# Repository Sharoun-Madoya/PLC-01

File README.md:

# PLC-01
BC848CDW1T1- transistor , power surface mount for amplification 
 DS1307ZN_ real time clock, 56 byte ram for data storage
 SLPRT5V0U2X low capacitance electrostatic discharge  protection diode  meant to protect two high frequency signls  from damage \

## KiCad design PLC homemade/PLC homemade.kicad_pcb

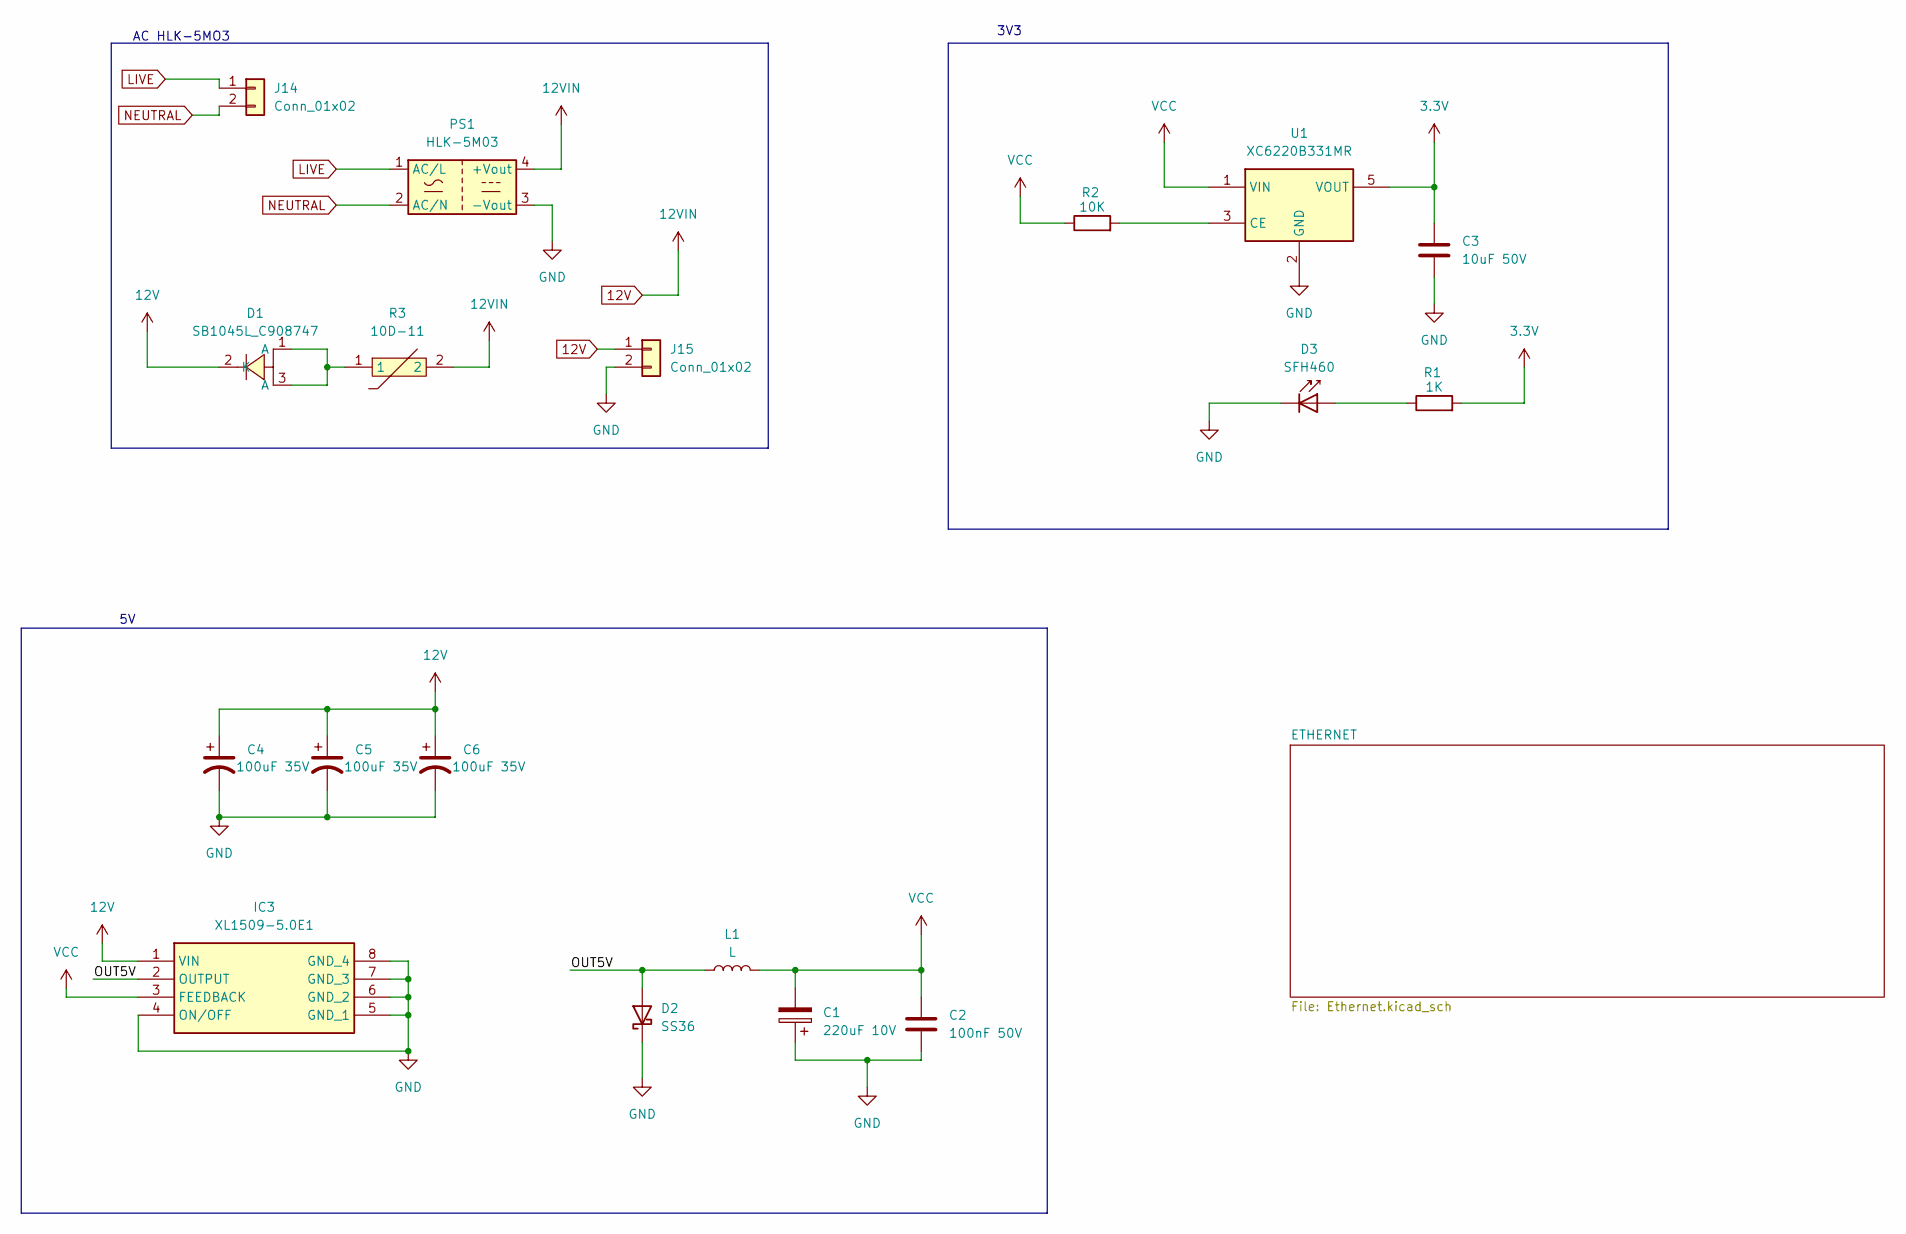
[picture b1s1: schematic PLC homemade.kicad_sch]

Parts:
C1: 220uF 10V; C_0201_0603Metric
C2: 100nF 50V; C_0201_0603Metric
C3: 10uF 50V; C_01005_0402Metric
C4, C5, C6: 100uF 35V; C_0201_0603Metric
D1: SB1045L_C908747; TO-277_3P-L5.4-W4.0-LS6.5-TR; LCSC Part C908747
D2: SS36; D_SMA
D3: SFH460; TO-18-2_Window
IC3: XL1509-5.0E1; SOIC127P600X175-8N; Manufacturer_Part_Number XL1509-5.0E1
J14: Conn_01x02; PhoenixContact_MCV_1,5_2-GF-3.81_1x02_P3.81mm_Vertical_Thre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
J15: Conn_01x02; PhoenixContact_GMSTBA_2,5_2-G_1x02_P7.50mm_Horizontal
L1: L; L_APV_APH1040
PS1: HLK-5M03; Converter_ACDC_Hi-Link_HLK-5Mxx
R1: 1K; Crystal_SMD_5032-2Pin_5.0x3.2mm
R2: 10K; R_01005_0402Metric
R3: 10D-11; RES-TH_L12.5-W5.5-P7.50-D0.8-S5.50; LCSC Part C53820
U1: XC6220B331MR; SOT-23-5

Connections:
3.3V: C3.1, R1.2, U1.5 (VOUT); also elsewhere on the board
12V: C4.1, C5.1, C6.1, D1.2 (K), IC3.1 (VIN), J15.1, PS1.4 (+Vout), R3.2; also elsewhere on the board
/OUT5V: D2.2 (A), IC3.2 (OUTPUT), L1.1
AGND: C1.1, C2.2, C3.2, C4.2, C5.2, C6.2, D2.1 (K), D3.1 (K), IC3.4 (ON/OFF), IC3.5 (GND_1), IC3.6 (GND_2), IC3.7 (GND_3), IC3.8 (GND_4), J15.2, PS1.3 (-Vout), U1.2 (GND); also elsewhere on the board
LIVE: J14.1, PS1.1 (AC/L)
NEUTRAL: J14.2, PS1.2 (AC/N)
unnamed: D1.1 (A), D1.3 (A), R3.1
unnamed: D3.2 (A), R1.1
unnamed: R2.2, U1.3 (CE)
VCC: C1.2, C2.1, IC3.3 (FEEDBACK), L1.2, R2.1, U1.1 (VIN); also elsewhere on the board

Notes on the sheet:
3V3
AC HLK-5MO3

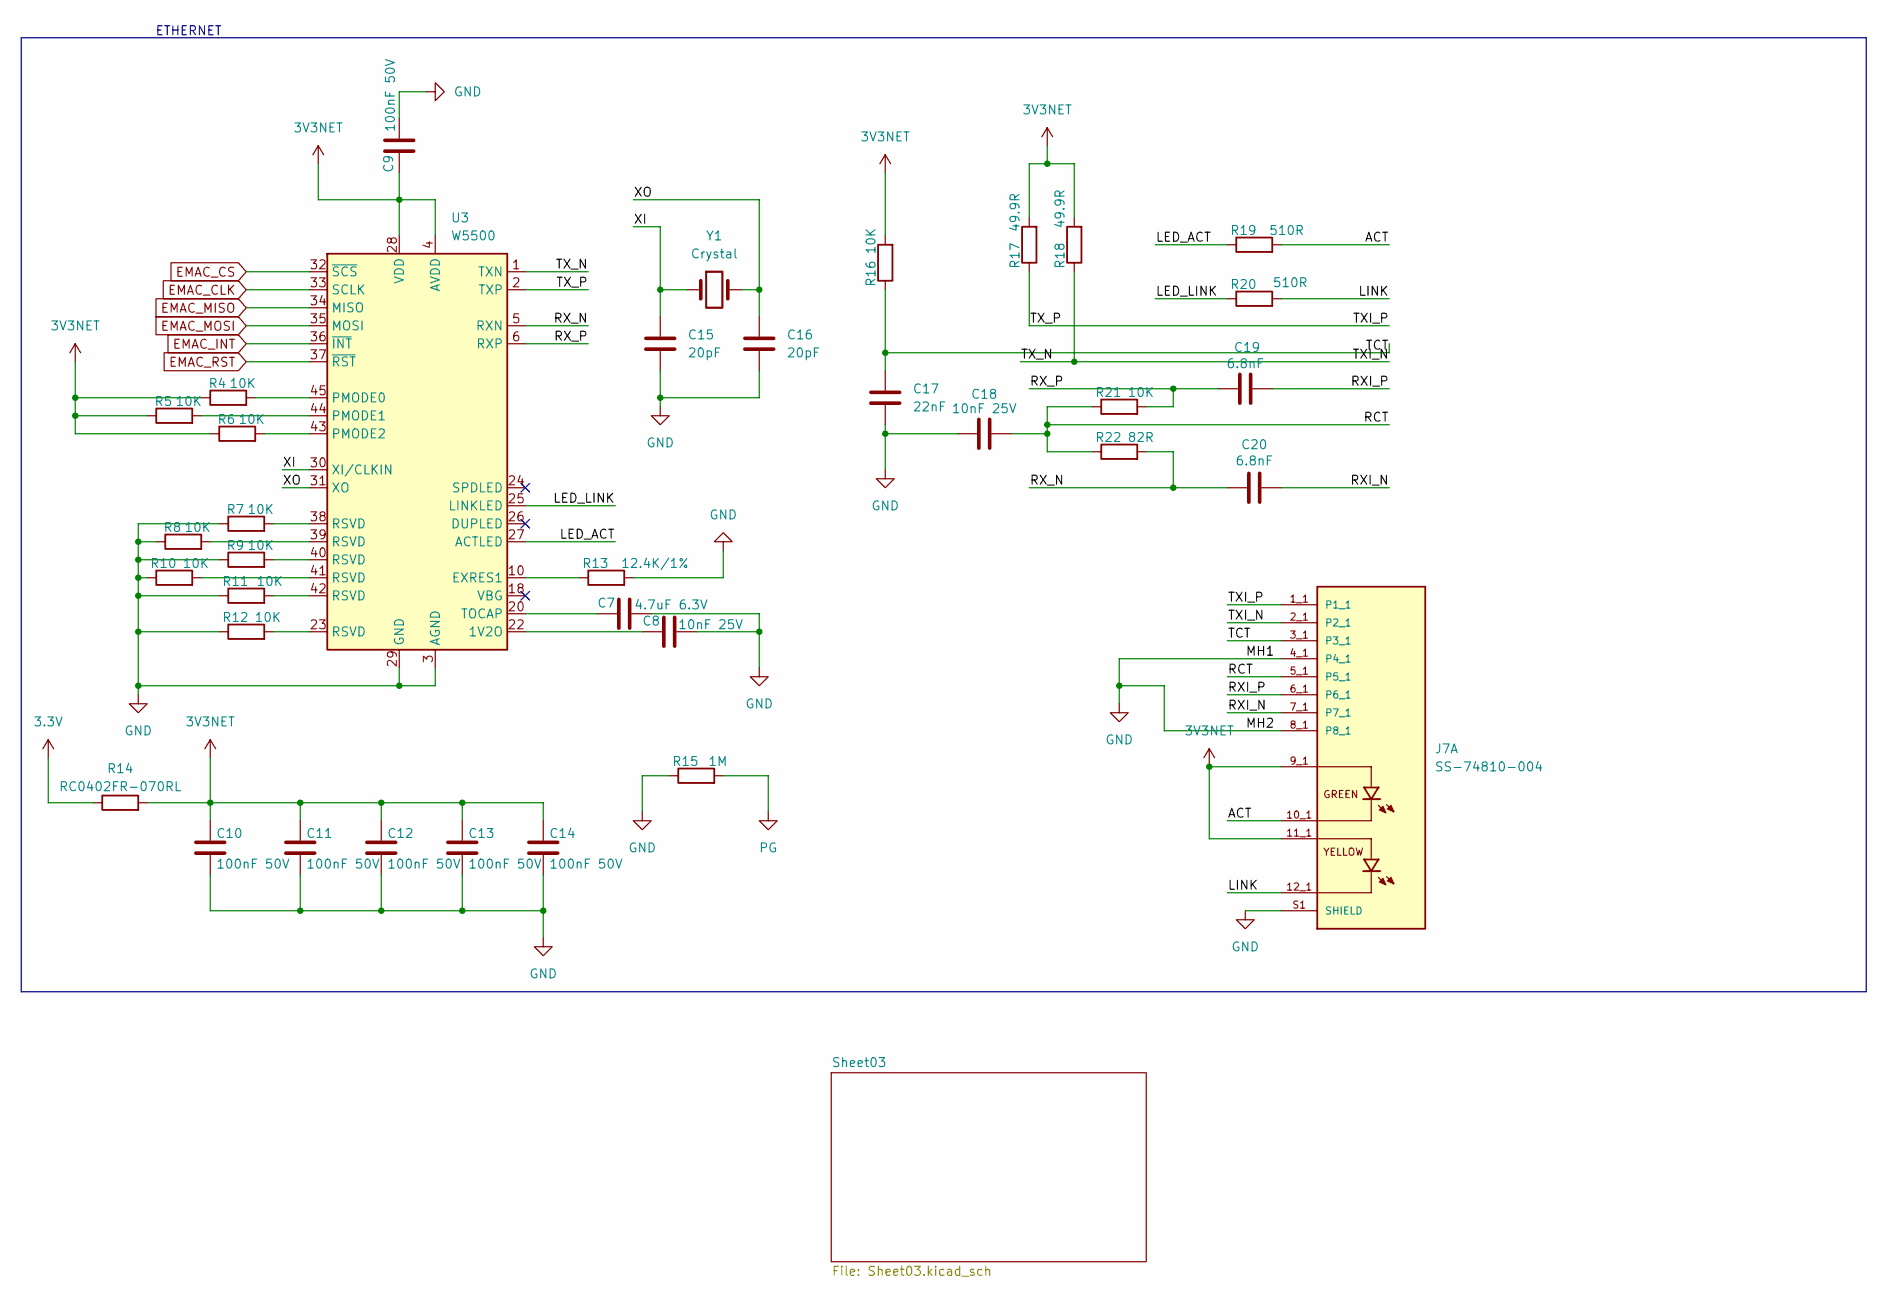
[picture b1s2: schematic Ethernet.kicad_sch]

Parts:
C7: 4.7uF 6.3V; C_01005_0402Metric
C8, C18: 10nF 25V; C_01005_0402Metric
C9, C10, C11, C12, C13, C14: 100nF 50V; C_01005_0402Metric
C15, C16: 20pF; C_01005_0402Metric
C17: 22nF; C_01005_0402Metric
C19, C20: 6.8nF; C_01005_0402Metric
J7: SS-74810-004; BEL_SS-74810-004; PARTREV A0
R4, R5, R6, R7, R8, R9, R10, R11, R12, R16, R21: 10K; R_01005_0402Metric
R13: 12.4K/1%; R_01005_0402Metric
R14: RC0402FR-070RL; R_01005_0402Metric
R15: 1M; R_01005_0402Metric
R17, R18: 49.9R; R_1206_3216Metric
R19, R20: 510R; R_1206_3216Metric
R22: 82R; R_1206_3216Metric
U3: W5500; LQFP-48_7x7mm_P0.5mm
Y1: Crystal; Crystal_SMD_5032-2Pin_5.0x3.2mm

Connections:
3.3V: R14.1; also elsewhere on the board
3V3NET: C9.1, C10.1, C11.1, C12.1, C13.1, C14.1, J7.9_1, J7.11_1, R4.1, R5.1, R6.1, R14.2, R16.2, R17.2, R18.2, U3.4 (AVDD), U3.8 (AVDD), U3.11 (AVDD), U3.15 (AVDD), U3.17 (AVDD), U3.21 (AVDD), U3.28 (VDD)
/ETHERNET/ACT: J7.10_1, R19.2
/ETHERNET/LED_ACT: R19.1, U3.27 (ACTLED)
/ETHERNET/LED_LINK: R20.1, U3.25 (LINKLED)
/ETHERNET/LINK: J7.12_1, R20.2
/ETHERNET/RCT: C18.2, J7.5_1, R21.1, R22.1
/ETHERNET/RXI_N: C20.2, J7.7_1
/ETHERNET/RXI_P: C19.2, J7.6_1
/ETHERNET/RX_N: C20.1, R22.2, U3.5 (RXN)
/ETHERNET/RX_P: C19.1, R21.2, U3.6 (RXP)
/ETHERNET/TCT: C17.1, J7.3_1, R16.1
/ETHERNET/TXI_N: J7.2_1, R18.1, U3.1 (TXN)
/ETHERNET/TXI_P: J7.1_1, R17.1, U3.2 (TXP)
/ETHERNET/XI: C15.1, U3.30 (XI/CLKIN), Y1.1
/ETHERNET/XO: C16.1, U3.31 (XO), Y1.2
AGND: C7.2, C8.2, C9.2, C10.2, C11.2, C12.2, C13.2, C14.2, C15.2, C16.2, C17.2, C18.1, J7.4_1, J7.8_1, J7.S1 (SHIELD), J7.S2 (SHIELD), J7.S3 (SHIELD), J7.S4 (SHIELD), J7.S5 (SHIELD), J7.S6 (SHIELD), J7.S7 (SHIELD), J7.S8 (SHIELD), J7.S9 (SHIELD), R7.1, R8.1, R9.1, R10.1, R11.1, R12.1, R13.2, R15.1, U3.3 (AGND), U3.9 (AGND), U3.14 (AGND), U3.16 (AGND), U3.19 (AGND), U3.29 (GND), U3.48 (AGND); also elsewhere on the board
EMAC_CLK: U3.33 (SCLK); also elsewhere on the board
EMAC_CS: U3.32 (~SCS); also elsewhere on the board
EMAC_INT: U3.36 (~INT); also elsewhere on the board
EMAC_MISO: U3.34 (MISO); also elsewhere on the board
EMAC_MOSI: U3.35 (MOSI); also elsewhere on the board
EMAC_RST: U3.37 (~RST); also elsewhere on the board
unnamed: R7.2, U3.38 (RSVD)
unnamed: R8.2, U3.39 (RSVD)
unnamed: R9.2, U3.40 (RSVD)
unnamed: R10.2, U3.41 (RSVD)
unnamed: R11.2, U3.42 (RSVD)
unnamed: R12.2, U3.23 (RSVD)
unnamed: C8.1, U3.22 (1V2O)
unnamed: R13.1, U3.10 (EXRES1)
unnamed: R4.2, U3.45 (PMODE0)
unnamed: R5.2, U3.44 (PMODE1)
unnamed: R6.2, U3.43 (PMODE2)
unnamed: C7.1, U3.20 (TOCAP)
PG: R15.2

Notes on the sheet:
ETHERNET

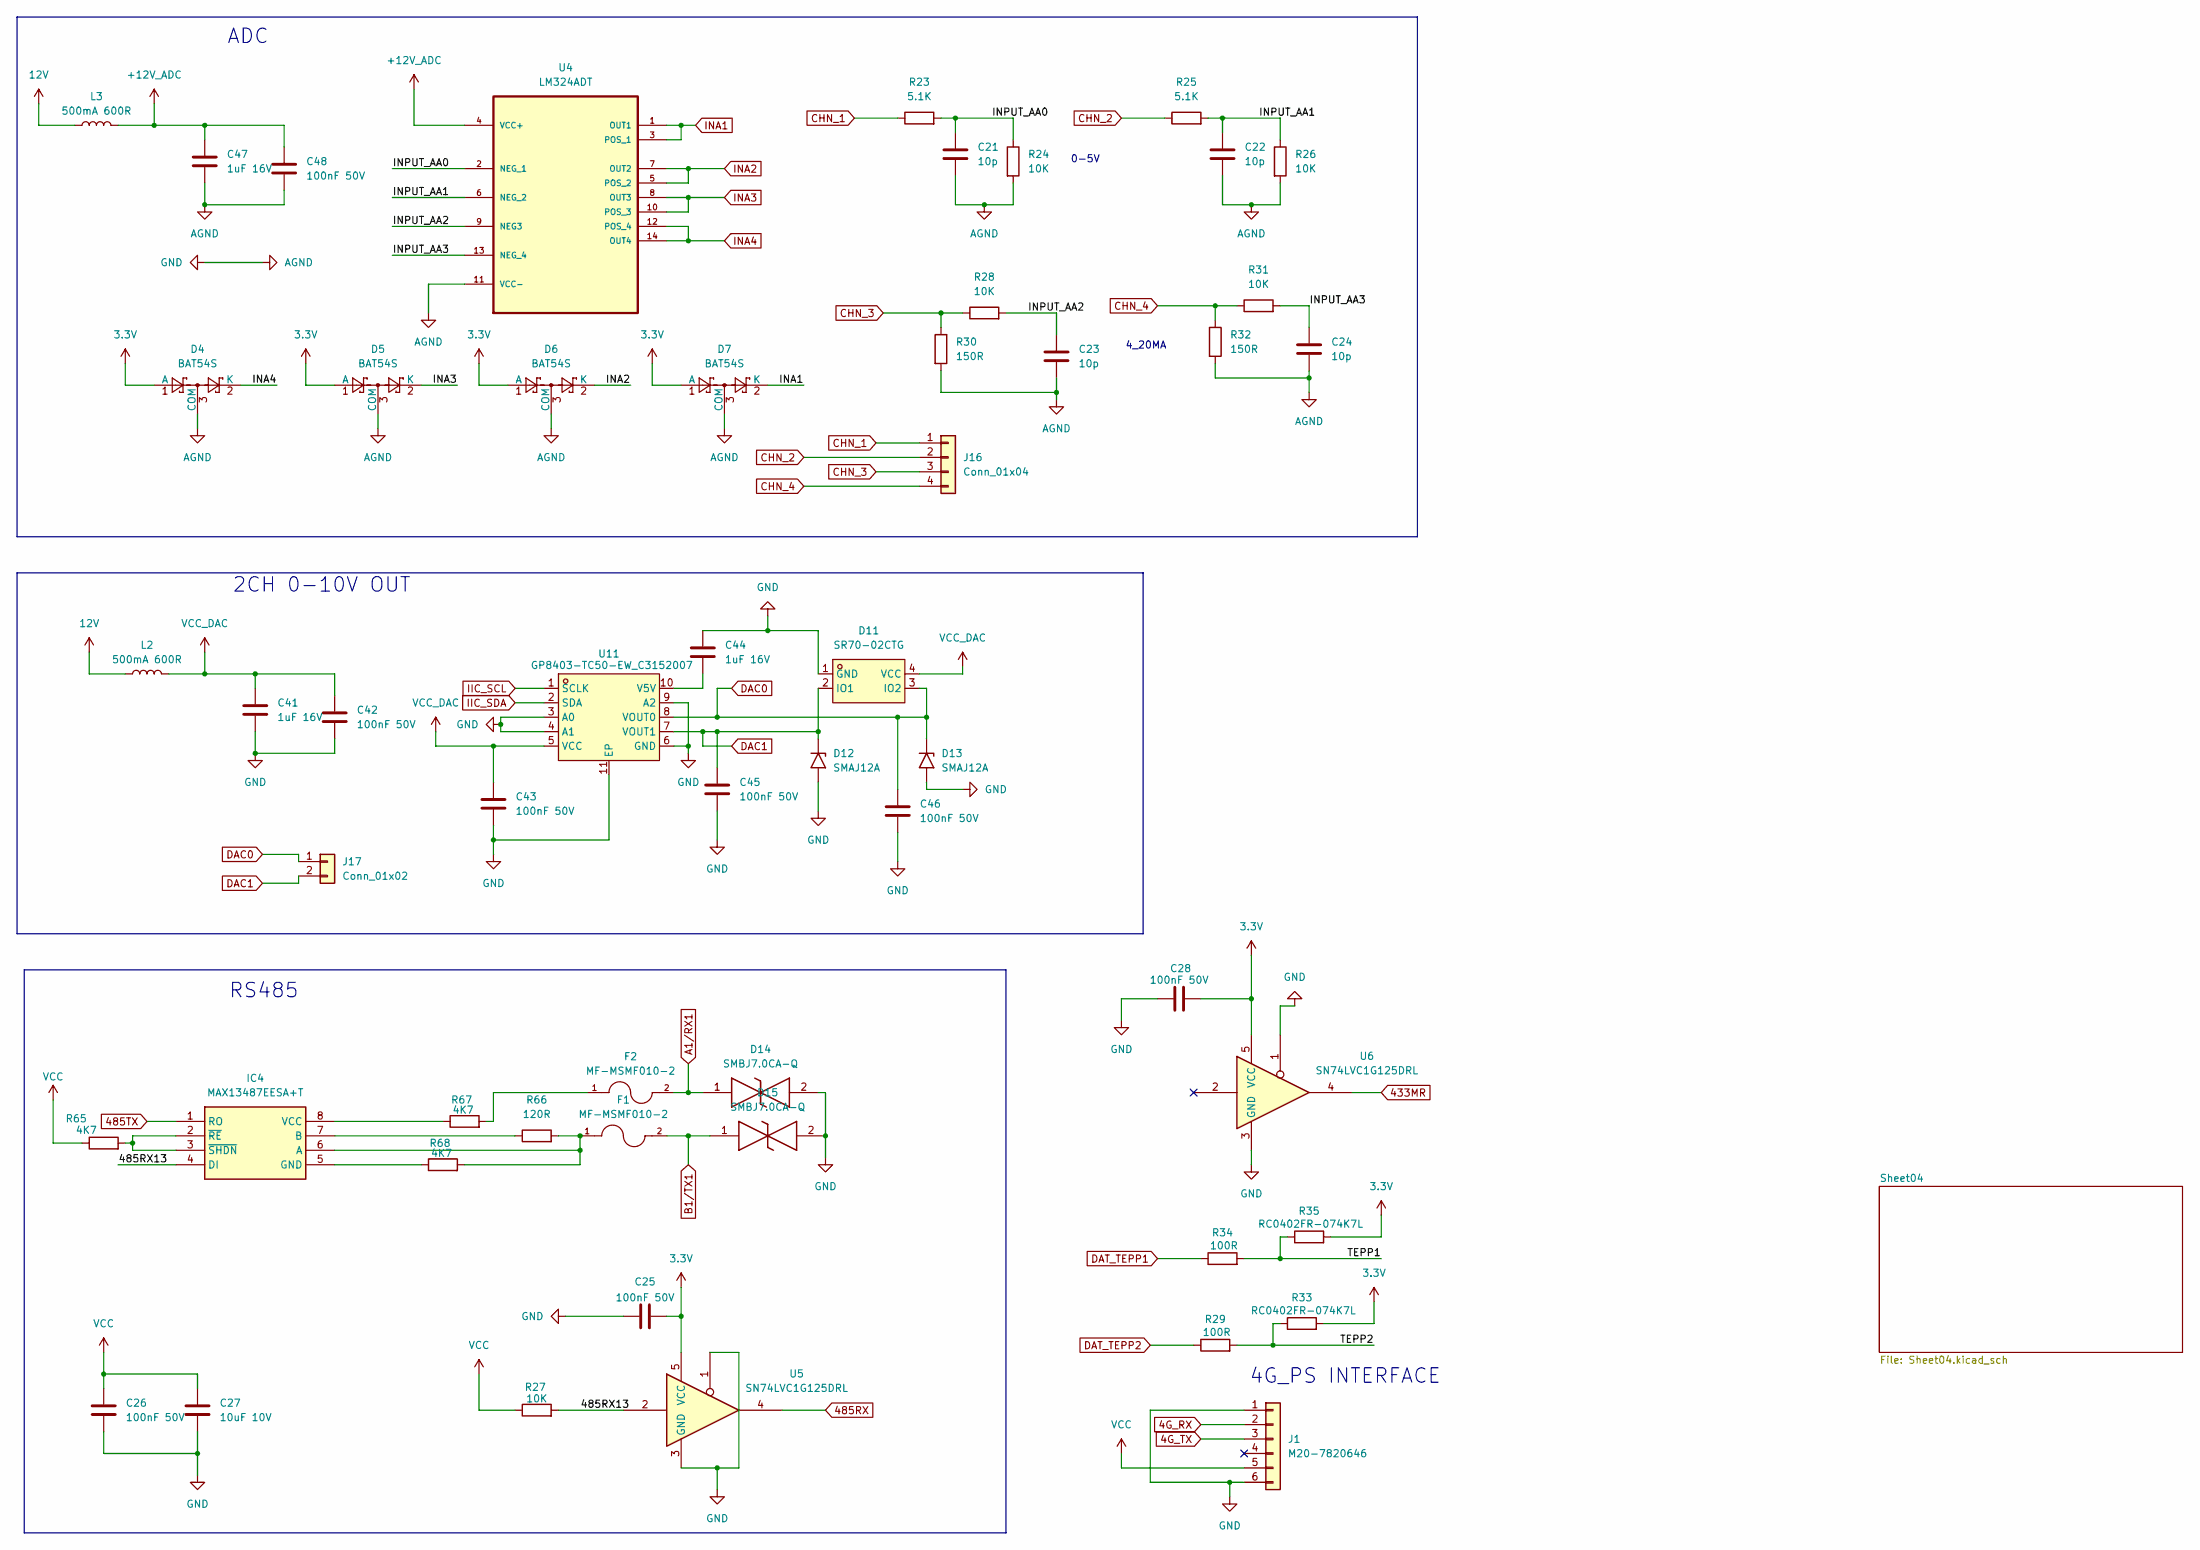
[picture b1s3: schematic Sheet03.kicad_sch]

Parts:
C21, C22, C23, C24: 10p; C_01005_0402Metric
C25, C26, C28, C42, C43, C45, C46: 100nF 50V; C_01005_0402Metric
C27: 10uF 10V; C_0201_0603Metric
C41, C44, C47: 1uF 16V; C_0201_0603Metric
C48: 100nF 50V; C_0201_0603Metric
D4, D5, D6, D7: BAT54S; SOT-23
D11: SR70-02CTG; SOT-143-4_L2.9-W1.3-P1.92-LS2.4-BL; LCSC Part C1973334
D12, D13: SMAJ12A; D_SMA
D14, D15: SMBJ7.0CA-Q; DIONM5436X244N; Manufacturer_Part_Number SMBJ7.0CA-Q
F1, F2: MF-MSMF010-2; FUSER_MF-MSMF010-2
IC4: MAX13487EESA+T; SOIC127P600X175-8N; Manufacturer_Part_Number MAX13487EESA+T; Mouser Part Number 700-MAX13487EESAT
J1: M20-7820646; HARWIN_M20-7820646
J16: Conn_01x04; PinHeader_1x04_P2.00mm_Vertical
J17: Conn_01x02; PinHeader_1x02_P2.00mm_Vertical
L2, L3: 500mA 600R; L_APV_APH1040
R23, R25: 5.1K; R_1206_3216Metric
R24, R26, R27, R28, R31: 10K; R_01005_0402Metric
R29, R34: 100R; R_1206_3216Metric
R30, R32: 150R; R_1206_3216Metric
R33, R35: RC0402FR-074K7L; R_1206_3216Metric
R65, R67, R68: 4K7; R_01005_0402Metric
R66: 120R; R_1206_3216Metric
U4: LM324ADT; SOIC127P600X175-14N; MPN LM324ADT
U5, U6: SN74LVC1G125DRL; Texas_R-PDSO-N5_DRL-5
U11: GP8403-TC50-EW_C3152007; ESSOP-10_L4.9-W3.9-P1.00-LS6.0-BL-EP; LCSC Part C3152007

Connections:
3.3V: C25.2, C28.2, D4.1 (A), D5.1 (A), D6.1 (A), D7.1 (A), R33.2, R35.2, U5.5 (VCC), U6.5 (VCC); also elsewhere on the board
4G_RX: J1.2
4G_TX: J1.3
12V: L2.1, L3.1; also elsewhere on the board
433MR: U6.4
485RX: U5.4; also elsewhere on the board
485TX: IC4.1 (RO); also elsewhere on the board
+12V_ADC: C47.1, C48.1, L3.2, U4.4 (VCC+)
/ETHERNET/Sheet03/485RX13: IC4.4 (DI), R27.2, U5.2
/ETHERNET/Sheet03/INPUT_AA0: C21.1, R23.2, R24.1, U4.2 (NEG_1)
/ETHERNET/Sheet03/INPUT_AA1: C22.1, R25.2, R26.1, U4.6 (NEG_2)
/ETHERNET/Sheet03/INPUT_AA2: C23.1, R28.2, U4.9 (NEG3)
/ETHERNET/Sheet03/INPUT_AA3: C24.1, R31.2, U4.13 (NEG_4)
/ETHERNET/Sheet03/TEPP1: R34.2, R35.1
/ETHERNET/Sheet03/TEPP2: R29.2, R33.1
A1/RX1: D14.1, F2.2
AGND: C21.2, C22.2, C23.2, C24.2, C25.1, C26.2, C27.2, C28.1, C41.2, C42.2, C43.2, C44.2, C45.2, C46.2, C47.2, C48.2, D4.3 (COM), D5.3 (COM), D6.3 (COM), D7.3 (COM), D11.1 (GND), D12.2 (A2), D13.2 (A2), D14.2, D15.2, J1.1, J1.6, R24.2, R26.2, R30.2, R32.2, U4.11 (VCC-), U5.1, U5.3 (GND), U6.1, U6.3 (GND), U11.3 (A0), U11.4 (A1), U11.6 (GND), U11.9 (A2), U11.11 (EP); also elsewhere on the board
B1/TX1: D15.1, F1.2
CHN_1: J16.1, R23.1
CHN_2: J16.2, R25.1
CHN_3: J16.3, R28.1, R30.1
CHN_4: J16.4, R31.1, R32.1
DAC0: C46.1, D11.3 (IO2), D13.1 (A1), J17.1, U11.8 (VOUT0)
DAC1: C45.1, D11.2 (IO1), D12.1 (A1), J17.2, U11.7 (VOUT1)
DAT_TEPP1: R34.1; also elsewhere on the board
DAT_TEPP2: R29.1; also elsewhere on the board
IIC_SCL: U11.1 (SCLK); also elsewhere on the board
IIC_SDA: U11.2 (SDA); also elsewhere on the board
INA1: D7.2 (K), U4.1 (OUT1), U4.3 (POS_1); also elsewhere on the board
INA2: D6.2 (K), U4.5 (POS_2), U4.7 (OUT2); also elsewhere on the board
INA3: D5.2 (K), U4.8 (OUT3), U4.10 (POS_3); also elsewhere on the board
INA4: D4.2 (K), U4.12 (POS_4), U4.14 (OUT4); also elsewhere on the board
unnamed: F2.1, R67.2
unnamed: F1.1, IC4.6 (A), R66.2, R68.2
unnamed: IC4.7 (B), R66.1
unnamed: IC4.5 (GND), R68.1
unnamed: IC4.8 (VCC), R67.1
unnamed: IC4.2 (~RE), IC4.3 (~SHDN), R65.2
unnamed: C44.1, U11.10 (V5V)
VCC: C26.1, C27.1, J1.5, R27.1, R65.1; also elsewhere on the board
VCC_DAC: C41.1, C42.1, C43.1, D11.4 (VCC), L2.2, U11.5 (VCC)

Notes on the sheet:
RS485
0-5V
2CH 0-10V OUT
4_20MA
4G_PS INTERFACE
ADC

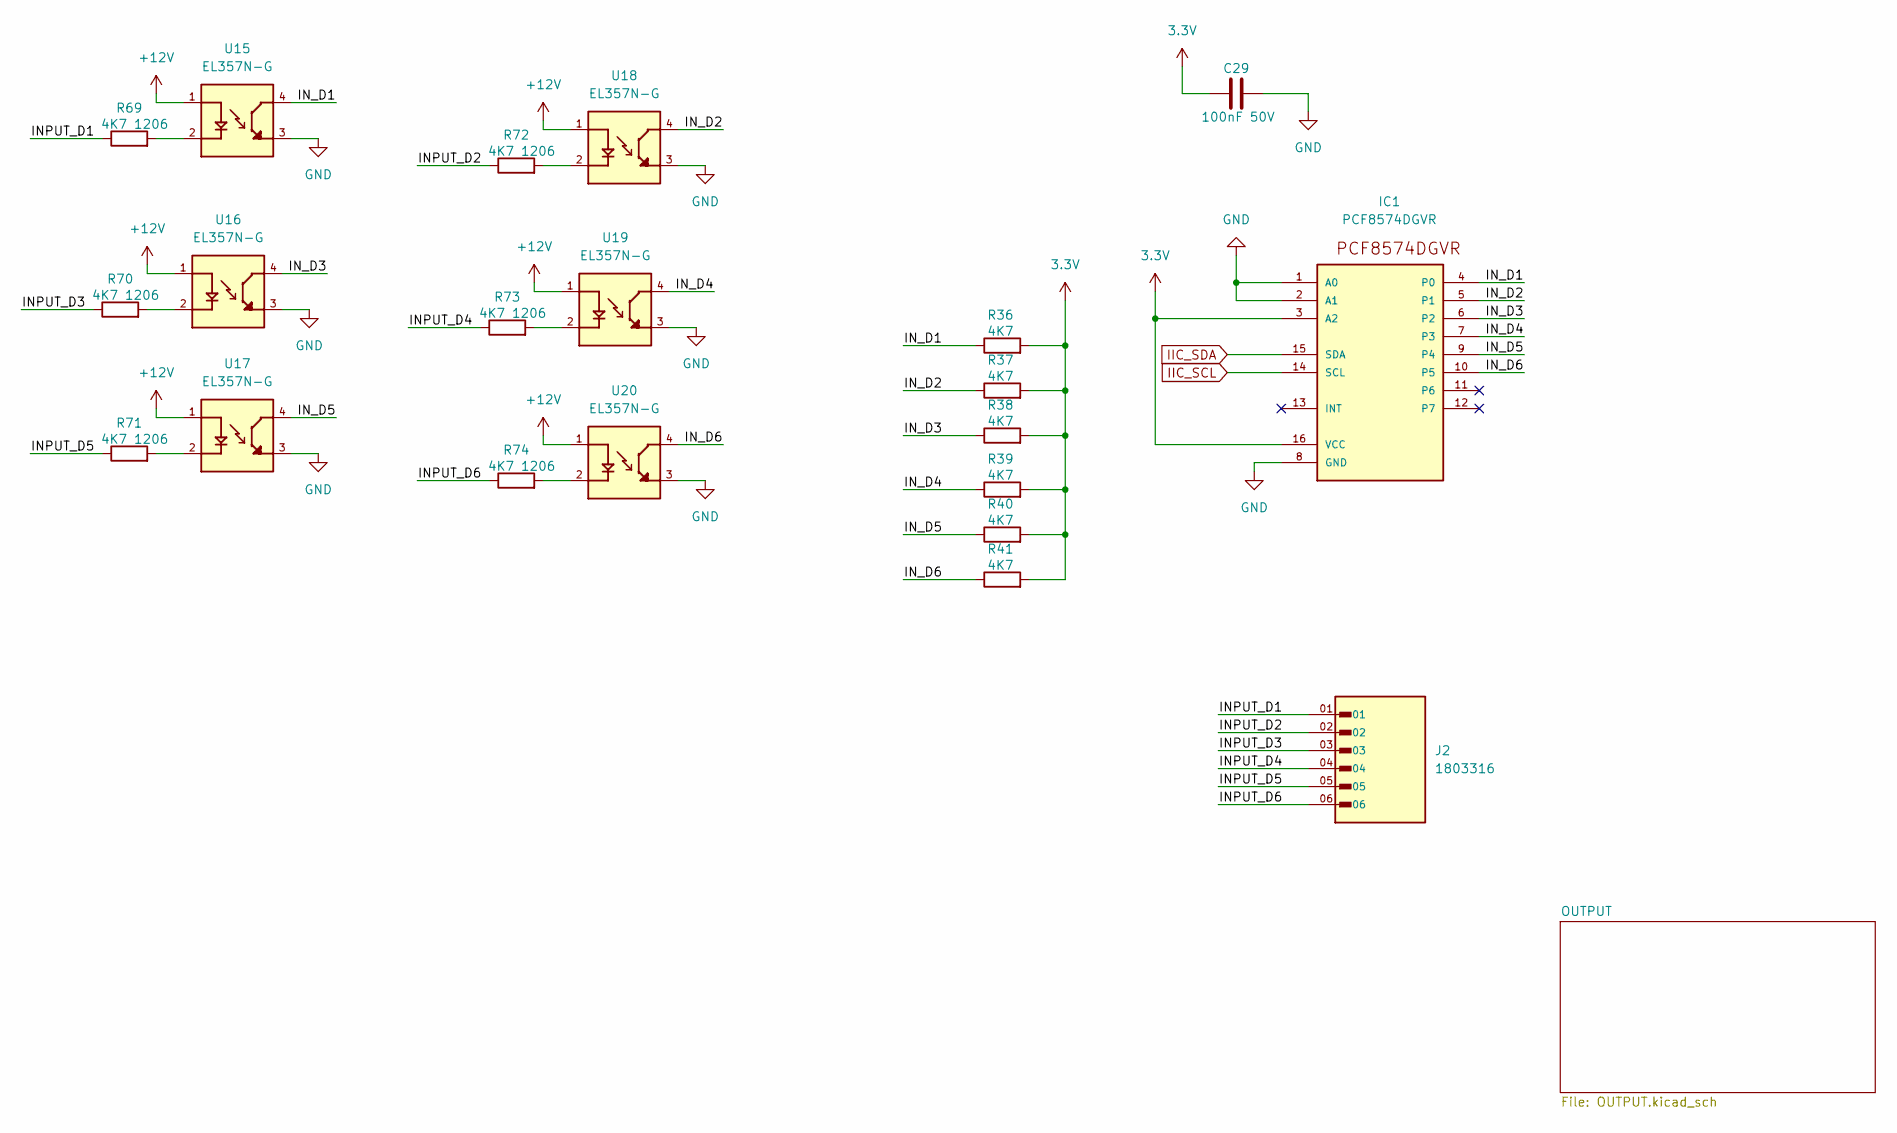
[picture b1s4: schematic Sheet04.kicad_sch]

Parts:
C29: 100nF 50V; C_01005_0402Metric
IC1: PCF8574DGVR; DIL16
J2: 1803316; PHOENIX_1803316; PARTREV 08.06.2015
R36, R37, R38, R39, R40, R41: 4K7; R_01005_0402Metric
R69, R70, R71, R72, R73, R74: 4K7 1206; R_01005_0402Metric
U15, U16, U17, U18, U19, U20: EL357N-G; OPTO_EL357N-G; PARTREV 6

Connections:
3.3V: C29.1, IC1.3 (A2), IC1.16 (VCC), R36.2, R37.2, R38.2, R39.2, R40.2, R41.2; also elsewhere on the board
+12V: U15.1, U16.1, U17.1, U18.1, U19.1, U20.1
/ETHERNET/Sheet03/Sheet04/INPUT_D1: J2.01, R69.1
/ETHERNET/Sheet03/Sheet04/INPUT_D2: J2.02, R72.1
/ETHERNET/Sheet03/Sheet04/INPUT_D3: J2.03, R70.1
/ETHERNET/Sheet03/Sheet04/INPUT_D4: J2.04, R73.1
/ETHERNET/Sheet03/Sheet04/INPUT_D5: J2.05, R71.1
/ETHERNET/Sheet03/Sheet04/INPUT_D6: J2.06, R74.1
/ETHERNET/Sheet03/Sheet04/IN_D1: IC1.4 (P0), R36.1, U15.4
/ETHERNET/Sheet03/Sheet04/IN_D2: IC1.5 (P1), R37.1, U18.4
/ETHERNET/Sheet03/Sheet04/IN_D3: IC1.6 (P2), R38.1, U16.4
/ETHERNET/Sheet03/Sheet04/IN_D4: IC1.7 (P3), R39.1, U19.4
/ETHERNET/Sheet03/Sheet04/IN_D5: IC1.9 (P4), R40.1, U17.4
/ETHERNET/Sheet03/Sheet04/IN_D6: IC1.10 (P5), R41.1, U20.4
AGND: C29.2, IC1.1 (A0), IC1.2 (A1), IC1.8 (GND), U15.3, U16.3, U17.3, U18.3, U19.3, U20.3; also elsewhere on the board
IIC_SCL: IC1.14 (SCL); also elsewhere on the board
IIC_SDA: IC1.15 (SDA); also elsewhere on the board
unnamed: R69.2, U15.2
unnamed: R70.2, U16.2
unnamed: R71.2, U17.2
unnamed: R72.2, U18.2
unnamed: R73.2, U19.2
unnamed: R74.2, U20.2

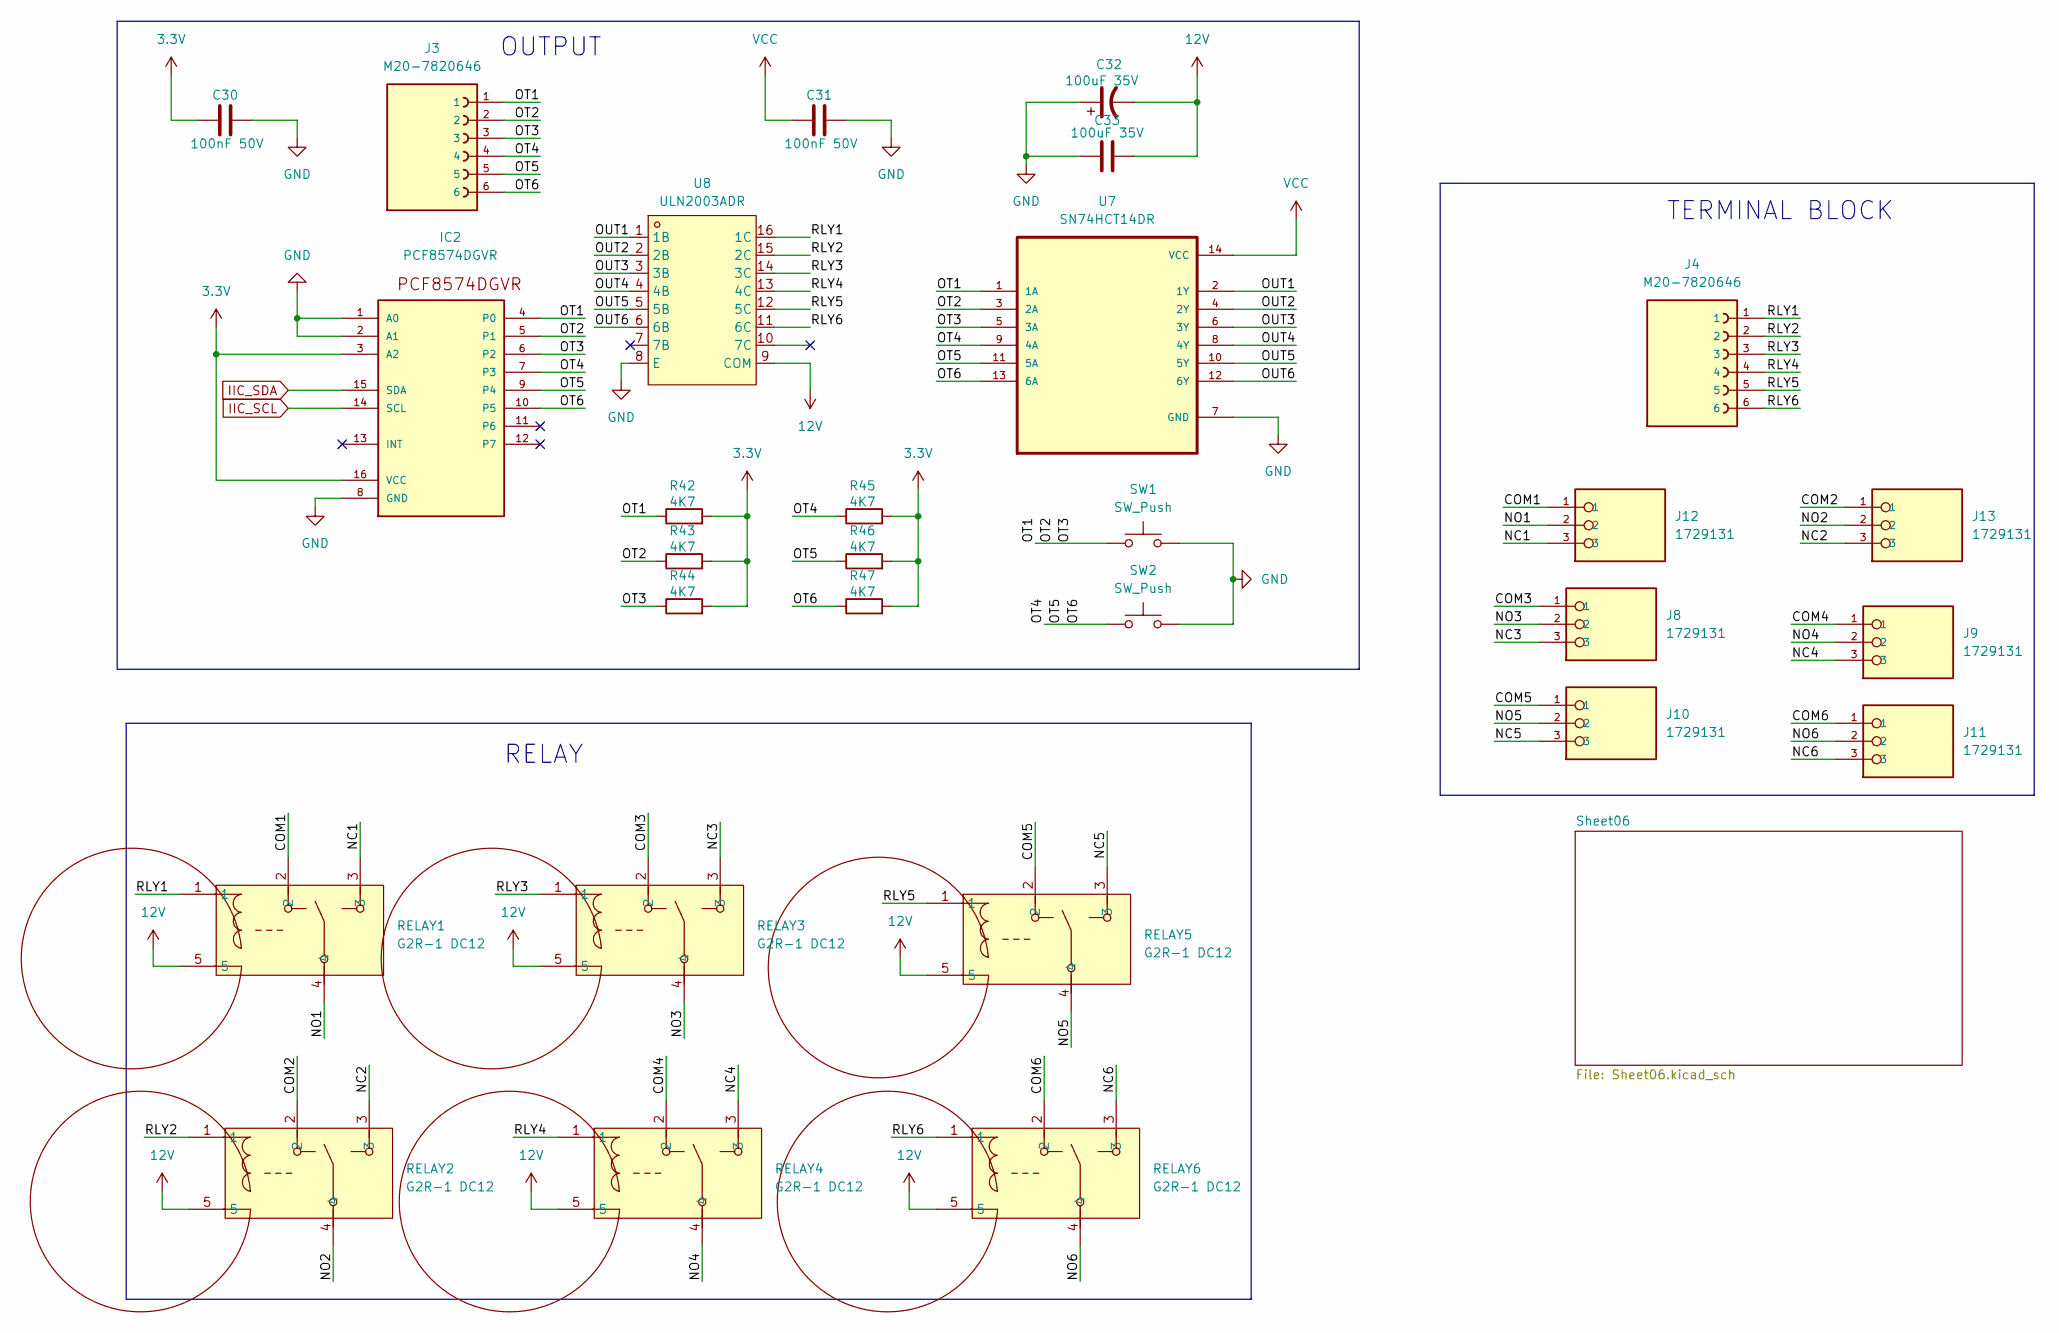
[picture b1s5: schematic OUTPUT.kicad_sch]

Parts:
C30, C31: 100nF 50V; C_01005_0402Metric
C32: 100uF 35V; CP_Elec_10x7.7
C33: 100uF 35V; C_0201_0603Metric
IC2: PCF8574DGVR; DIL16
J3, J4: M20-7820646; HARWIN_M20-7820646
J8, J9, J10, J11, J12, J13: 1729131; PHOENIX_1729131
R42, R43, R44, R45, R46, R47: 4K7; R_01005_0402Metric
RELAY1, RELAY2, RELAY3, RELAY4, RELAY5, RELAY6: G2R-1 DC12; RELAY-TH_G2R-1; LCSC Part C2750337
SW1, SW2: SW_Push; SW_SPST_TL3305A
U7: SN74HCT14DR; SOIC127P600X175-14N
U8: ULN2003ADR; SOIC-16_L9.9-W3.9-P1.27-LS6.0-BL; LCSC Part C7512

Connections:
3.3V: C30.1, IC2.3 (A2), IC2.16 (VCC), R42.2, R43.2, R44.2, R45.2, R46.2, R47.2; also elsewhere on the board
12V: C32.2, C33.1, RELAY1.5, RELAY2.5, RELAY3.5, RELAY4.5, RELAY5.5, RELAY6.5, U8.9 (COM); also elsewhere on the board
/ETHERNET/Sheet03/Sheet04/OUTPUT/COM1: J12.1, RELAY1.2
/ETHERNET/Sheet03/Sheet04/OUTPUT/COM2: J13.1, RELAY2.2
/ETHERNET/Sheet03/Sheet04/OUTPUT/COM3: J8.1, RELAY3.2
/ETHERNET/Sheet03/Sheet04/OUTPUT/COM4: J9.1, RELAY4.2
/ETHERNET/Sheet03/Sheet04/OUTPUT/COM5: J10.1, RELAY5.2
/ETHERNET/Sheet03/Sheet04/OUTPUT/COM6: J11.1, RELAY6.2
/ETHERNET/Sheet03/Sheet04/OUTPUT/NC1: J12.3, RELAY1.3
/ETHERNET/Sheet03/Sheet04/OUTPUT/NC2: J13.3, RELAY2.3
/ETHERNET/Sheet03/Sheet04/OUTPUT/NC3: J8.3, RELAY3.3
/ETHERNET/Sheet03/Sheet04/OUTPUT/NC4: J9.3, RELAY4.3
/ETHERNET/Sheet03/Sheet04/OUTPUT/NC5: J10.3, RELAY5.3
/ETHERNET/Sheet03/Sheet04/OUTPUT/NC6: J11.3, RELAY6.3
/ETHERNET/Sheet03/Sheet04/OUTPUT/NO1: J12.2, RELAY1.4
/ETHERNET/Sheet03/Sheet04/OUTPUT/NO2: J13.2, RELAY2.4
/ETHERNET/Sheet03/Sheet04/OUTPUT/NO3: J8.2, RELAY3.4
/ETHERNET/Sheet03/Sheet04/OUTPUT/NO4: J9.2, RELAY4.4
/ETHERNET/Sheet03/Sheet04/OUTPUT/NO5: J10.2, RELAY5.4
/ETHERNET/Sheet03/Sheet04/OUTPUT/NO6: J11.2, RELAY6.4
/ETHERNET/Sheet03/Sheet04/OUTPUT/OT1: IC2.4 (P0), IC2.5 (P1), IC2.6 (P2), J3.1, J3.2, J3.3, R42.1, R43.1, R44.1, SW1.1, U7.1 (1A), U7.3 (2A), U7.5 (3A)
/ETHERNET/Sheet03/Sheet04/OUTPUT/OT4: IC2.7 (P3), IC2.9 (P4), IC2.10 (P5), J3.4, J3.5, J3.6, R45.1, R46.1, R47.1, SW2.1, U7.9 (4A), U7.11 (5A), U7.13 (6A)
/ETHERNET/Sheet03/Sheet04/OUTPUT/OUT1: U7.2 (1Y), U8.1 (1B)
/ETHERNET/Sheet03/Sheet04/OUTPUT/OUT2: U7.4 (2Y), U8.2 (2B)
/ETHERNET/Sheet03/Sheet04/OUTPUT/OUT3: U7.6 (3Y), U8.3 (3B)
/ETHERNET/Sheet03/Sheet04/OUTPUT/OUT4: U7.8 (4Y), U8.4 (4B)
/ETHERNET/Sheet03/Sheet04/OUTPUT/OUT5: U7.10 (5Y), U8.5 (5B)
/ETHERNET/Sheet03/Sheet04/OUTPUT/OUT6: U7.12 (6Y), U8.6 (6B)
/ETHERNET/Sheet03/Sheet04/OUTPUT/RLY1: J4.1, RELAY1.1, U8.16 (1C)
/ETHERNET/Sheet03/Sheet04/OUTPUT/RLY2: J4.2, RELAY2.1, U8.15 (2C)
/ETHERNET/Sheet03/Sheet04/OUTPUT/RLY3: J4.3, RELAY3.1, U8.14 (3C)
/ETHERNET/Sheet03/Sheet04/OUTPUT/RLY4: J4.4, RELAY4.1, U8.13 (4C)
/ETHERNET/Sheet03/Sheet04/OUTPUT/RLY5: J4.5, RELAY5.1, U8.12 (5C)
/ETHERNET/Sheet03/Sheet04/OUTPUT/RLY6: J4.6, RELAY6.1, U8.11 (6C)
AGND: C30.2, C31.2, C32.1, C33.2, IC2.1 (A0), IC2.2 (A1), IC2.8 (GND), SW1.2, SW2.2, U7.7 (GND), U8.8 (E); also elsewhere on the board
IIC_SCL: IC2.14 (SCL); also elsewhere on the board
IIC_SDA: IC2.15 (SDA); also elsewhere on the board
VCC: C31.1, U7.14 (VCC); also elsewhere on the board

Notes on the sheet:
RELAY
TERMINAL BLOCK
OUTPUT
